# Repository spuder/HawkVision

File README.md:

# HawkVision

Adapter board that makes it easy to mount a TBS unify nano to the Hawk 5

[Available for purchase on etsy](https://www.etsy.com/listing/630369832/hawk-vision-vtx-realpit?ref=shop_home_active_1)

Based off the same idea as [whitenoise FPV](https://whitenoisefpv.com/collections/electronics/products/unify-nano-mounting-board) but designed specifically for the emax stack

## Schematic

## BOM

Any N-Channel mosfet _should_ work as log as it is a 'logic level mosfet'. A logic level mosfet has a VGS (aka gate voltage or Gate-Source threshold voltage MAX which is less than 5v or 3.3 volts). (e.g a VGS of 4.0 would work on a 5v arduino, but not a 3.3v arduino. 

- [N Channel Mosfet 863-NTR4501NT1G](https://www.mouser.com/ProductDetail/863-NTR4501NT1G)  <- Most shipped units were this model
- [N Channel Mosftet  PVM64UNE](https://www.mouser.com/ProductDetail/771-PMV65UNER) 
- [10K Resistors](https://www.mouser.com/ProductDetail/660-CFS1-4C103J)  
- [N Channel Mosfet SSM3K344R](https://www.mouser.com/ProductDetail/757-SSM3K344RLF)  
- [N Channel Mosfet 2N7000](https://www.mouser.com/ProductDetail/512-2N7000)  

Additional parts

- https://www.sparkfun.com/products/10213
- https://www.adafruit.com/product/355

### Resources

https://dronebotworkshop.com/transistors-mosfets/  
https://forum.arduino.cc/t/need-a-3-3v-logic-level-mosfet/933013/2  
https://electronics.stackexchange.com/a/235682/23954

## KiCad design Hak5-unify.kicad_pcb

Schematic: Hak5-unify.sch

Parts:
J1: Conn_01x04; Pin_Header_Straight_1x04_Pitch2.54mm
J2: Conn_01x03; Pin_Header_Straight_1x03_Pitch2.54mm
JP1: SolderJumper_2_Open; SolderJumper-2_P1.3mm_Open_RoundedPad1.0x1.5mm
Q2: PMV65UNER; SOT-23
R1, R2, R3: 10K; R_Axial_DIN0204_L3.6mm_D1.6mm_P7.62mm_Horizontal
SW1: SW_Push; CP_Elec_3x5.3
U1: Unify-Nano; unify-nano

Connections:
+5V: J1.3, J2.1, U1.6
GND: J1.4, J2.2, JP1.2 (B), Q2.2 (S), R1.2, R2.1
unnamed: J2.3, U1.2
unnamed: JP1.1 (A), Q2.3 (D), U1.5
unnamed: Q2.1 (G), R2.2, R3.1
unnamed: SW1.1, U1.10
unnamed: SW1.2, U1.9
RX: J1.2, R3.2
TX: J1.1, R1.1, U1.1

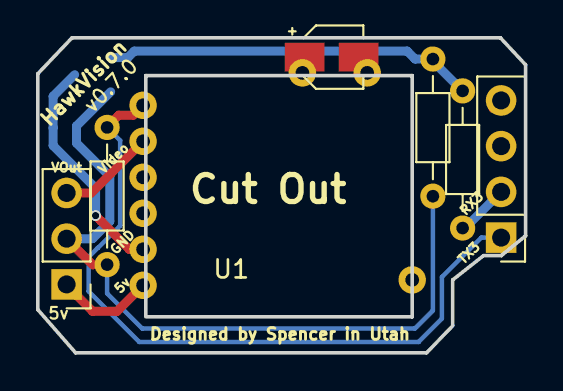
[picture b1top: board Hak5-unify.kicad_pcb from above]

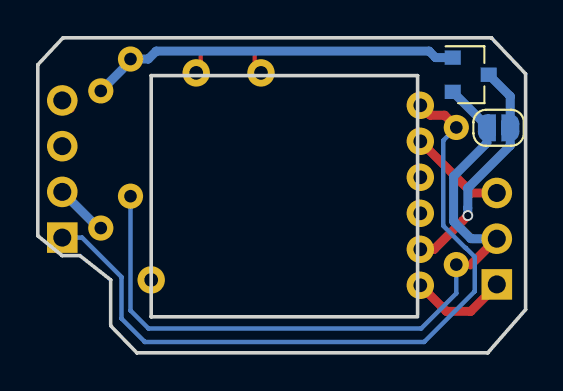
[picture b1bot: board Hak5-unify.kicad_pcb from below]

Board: 2 copper layers, 27.1 x 17.5 mm, 9 parts (2 on the bottom side), 9 nets.

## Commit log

2018-08-20 readme
2018-08-28 v0.1.1
2018-08-28 v0.2.0
2018-08-31 designed by spencer
2018-09-02 plot 0.2.1
2018-09-03 no panelization
2018-09-04 slightly different corner cutout
2018-09-06 v0.3.0
2018-09-08 2holes
2018-09-08 fixes 2holes
2018-09-08 v0.4.0
2018-09-09 v0.4.1
2018-09-17 v0.6.0
2018-09-17 saved
2018-09-17 screenshot
2018-10-14 link
2018-10-19 0.7.0
2022-07-21 update mosfets in readme
2022-07-21 add links
2022-07-22 schematic
